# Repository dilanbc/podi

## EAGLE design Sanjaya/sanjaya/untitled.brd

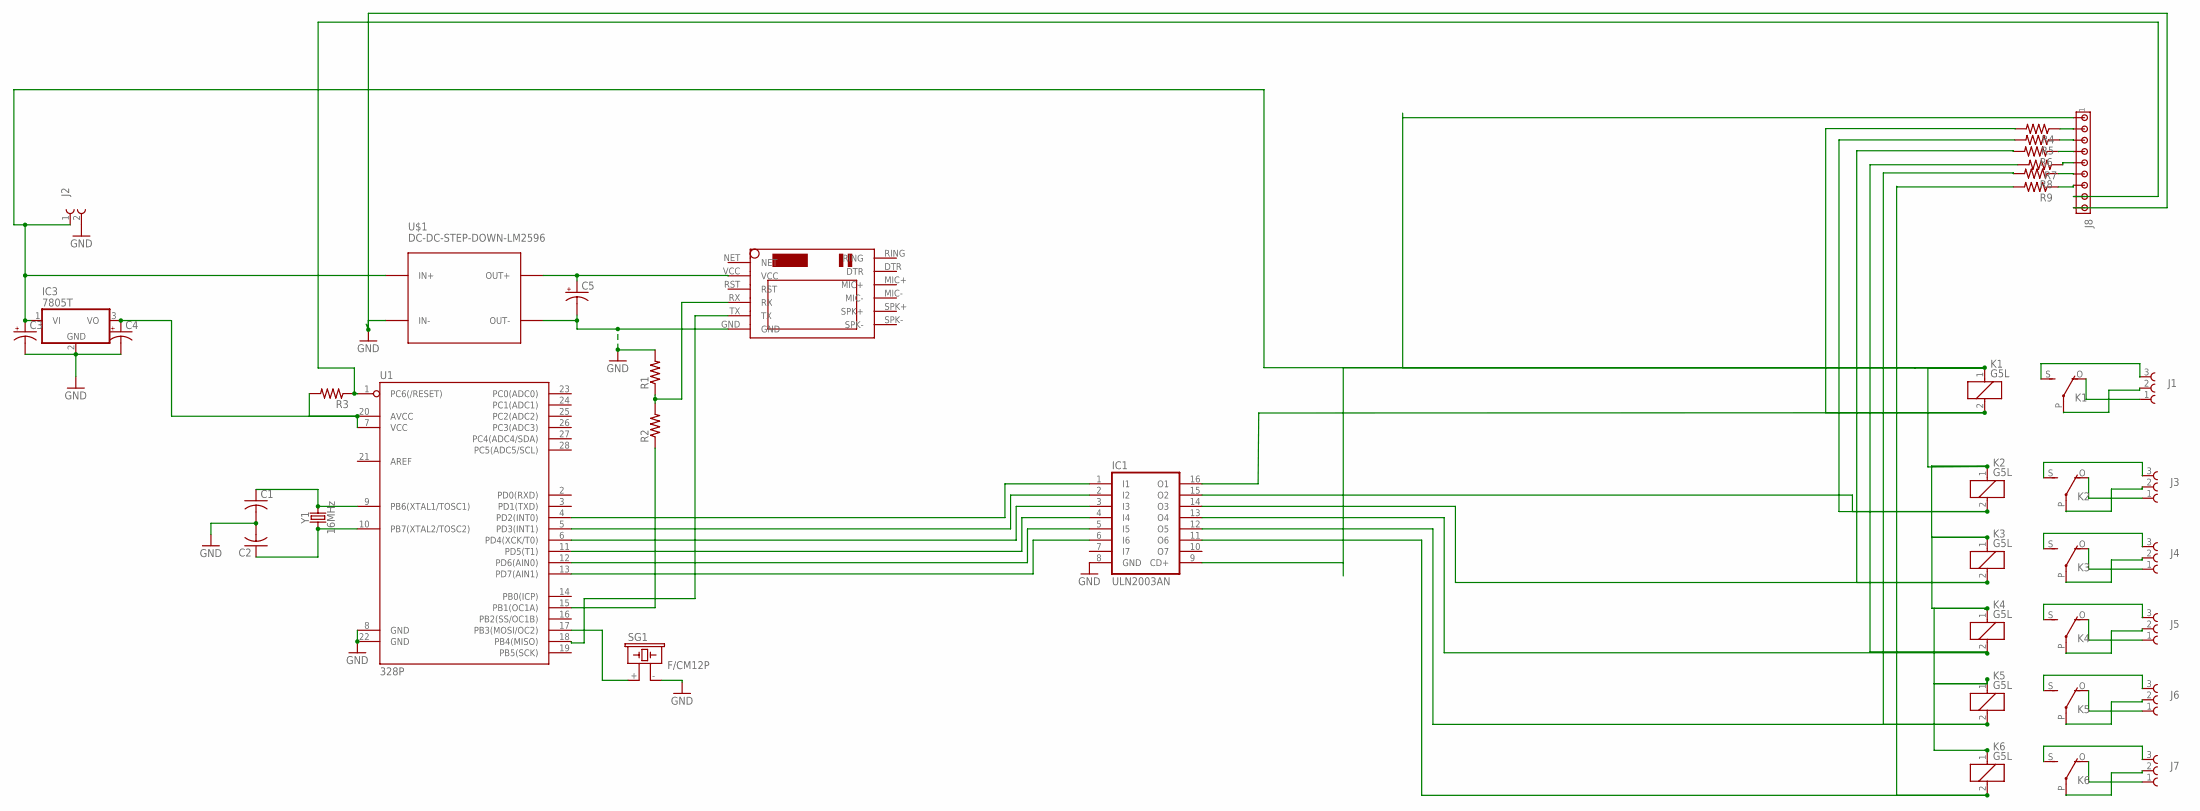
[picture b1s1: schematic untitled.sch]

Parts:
C1, C2: C-US025-024X044; C025-024X044
C3, C4: CPOL-USE2.5-5; E2,5-5
C5: CAPACITOR-PE5-8.5; E5-8,5
IC1: ULN2003AN; DIL16
IC3: 7805T; TO220H
J1, J3, J4, J5, J6, J7: 691216700003
J2: 691217910002
J8: MTA09-100; 10X09MTA
K1, K2, K3, K4, K5, K6: G5L; G5LE
R1, R2, R3, R4, R5, R6, R7, R8, R9: R-US_0204/7; 0204/7
SG1: F/CM12P
U1: 328P; DIP28
U$1: DC-DC-STEP-DOWN-LM2596
U$2: SIM800LMODULE
Y1: 16MHz; HC49US

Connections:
GND: C1.2, C2.2, C3.-, C4.-, C5.-, IC1.8 (GND), IC3.2 (GND), J2.2, J8.9, R1.2, SG1.- (2), U1.8 (GND), U1.22 (GND), U$1.IN-, U$1.OUT-, U$2.GND
unnamed: IC1.1 (I1), U1.4 (PD2(INT0))
unnamed: C2.1, U1.10 (PB7(XTAL2/TOSC2)), Y1.1
unnamed: C1.1, U1.9 (PB6(XTAL1/TOSC1)), Y1.2
unnamed: IC1.2 (I2), U1.5 (PD3(INT1))
unnamed: IC1.3 (I3), U1.6 (PD4(XCK/T0))
unnamed: IC1.4 (I4), U1.11 (PD5(T1))
unnamed: IC1.5 (I5), U1.12 (PD6(AIN0))
unnamed: IC1.6 (I6), U1.13 (PD7(AIN1))
unnamed: IC1.15 (O2), K2.2, R5.2
unnamed: C4.+, IC3.3 (VO), R3.2, U1.7 (VCC), U1.20 (AVCC)
unnamed: J8.2, R4.1
unnamed: IC1.14 (O3), K3.2, R6.2
unnamed: IC1.13 (O4), K4.2, R7.2
unnamed: C5.+, U$1.OUT+, U$2.VCC
unnamed: U1.18 (PB4(MISO)), U$2.TX
unnamed: R2.1, U1.15 (PB1(OC1A))
unnamed: R1.1, R2.2, U$2.RX
unnamed: IC1.12 (O5), K5.2, R8.2
unnamed: J1.2, K1.P
unnamed: J1.3 (1), K1.S
unnamed: J1.1 (3), K1.O
unnamed: J8.3, R5.1
unnamed: IC1.16 (O1), K1.2, R4.2
unnamed: J3.2, K2.P
unnamed: J3.3 (1), K2.S
unnamed: J3.1 (3), K2.O
unnamed: J8.8, R3.1, U1.1 (PC6(/RESET))
unnamed: J4.2, K3.P
unnamed: J4.3 (1), K3.S
unnamed: J4.1 (3), K3.O
unnamed: SG1.+ (1), U1.17 (PB3(MOSI/OC2))
unnamed: J5.2, K4.P
unnamed: J5.3 (1), K4.S
unnamed: J5.1 (3), K4.O
unnamed: J8.4, R6.1
unnamed: J6.2, K5.P
unnamed: J6.3 (1), K5.S
unnamed: J6.1 (3), K5.O
unnamed: C3.+, IC1.9 (CD+), IC3.1 (VI), J2.1, J8.1, K1.1, K2.1, K3.1, K4.1, K5.1, K6.1, U$1.IN+
unnamed: J7.2, K6.P
unnamed: J7.3 (1), K6.S
unnamed: J7.1 (3), K6.O
unnamed: J8.5, R7.1
unnamed: J8.6, R8.1
unnamed: J8.7, R9.1
unnamed: IC1.11 (O6), K6.2, R9.2

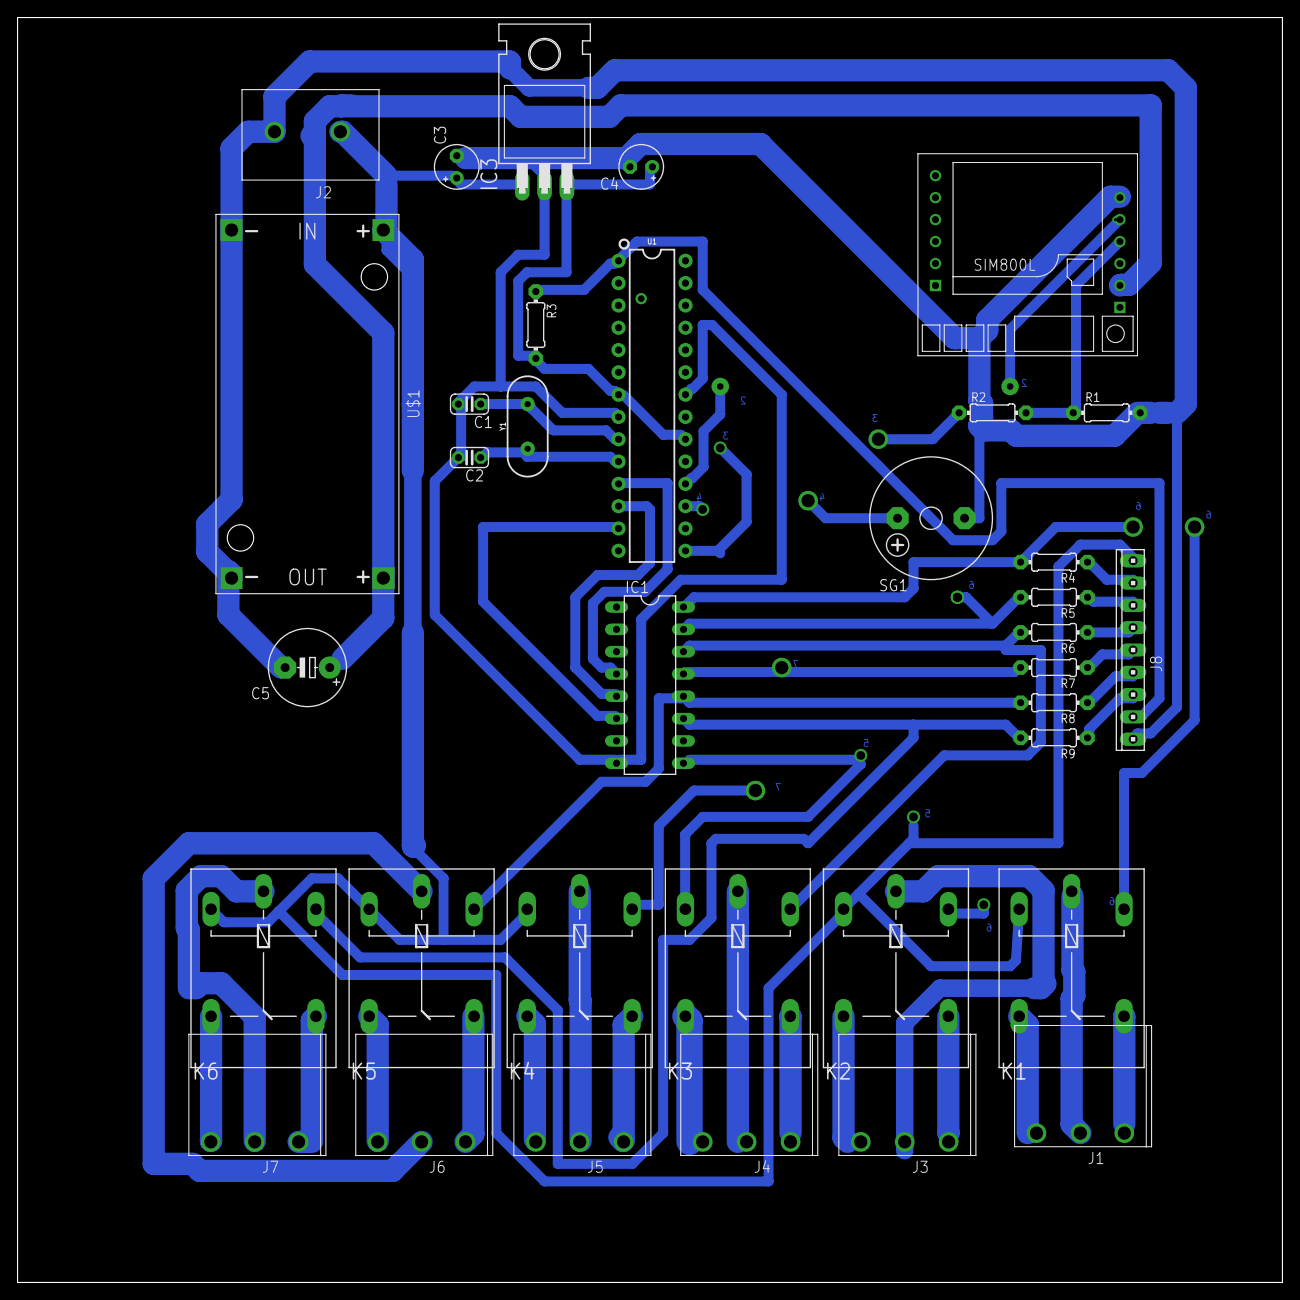
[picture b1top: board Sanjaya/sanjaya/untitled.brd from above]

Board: 2 copper layers, 144.0 x 144.0 mm, 35 parts (0 on the bottom side), 47 nets.

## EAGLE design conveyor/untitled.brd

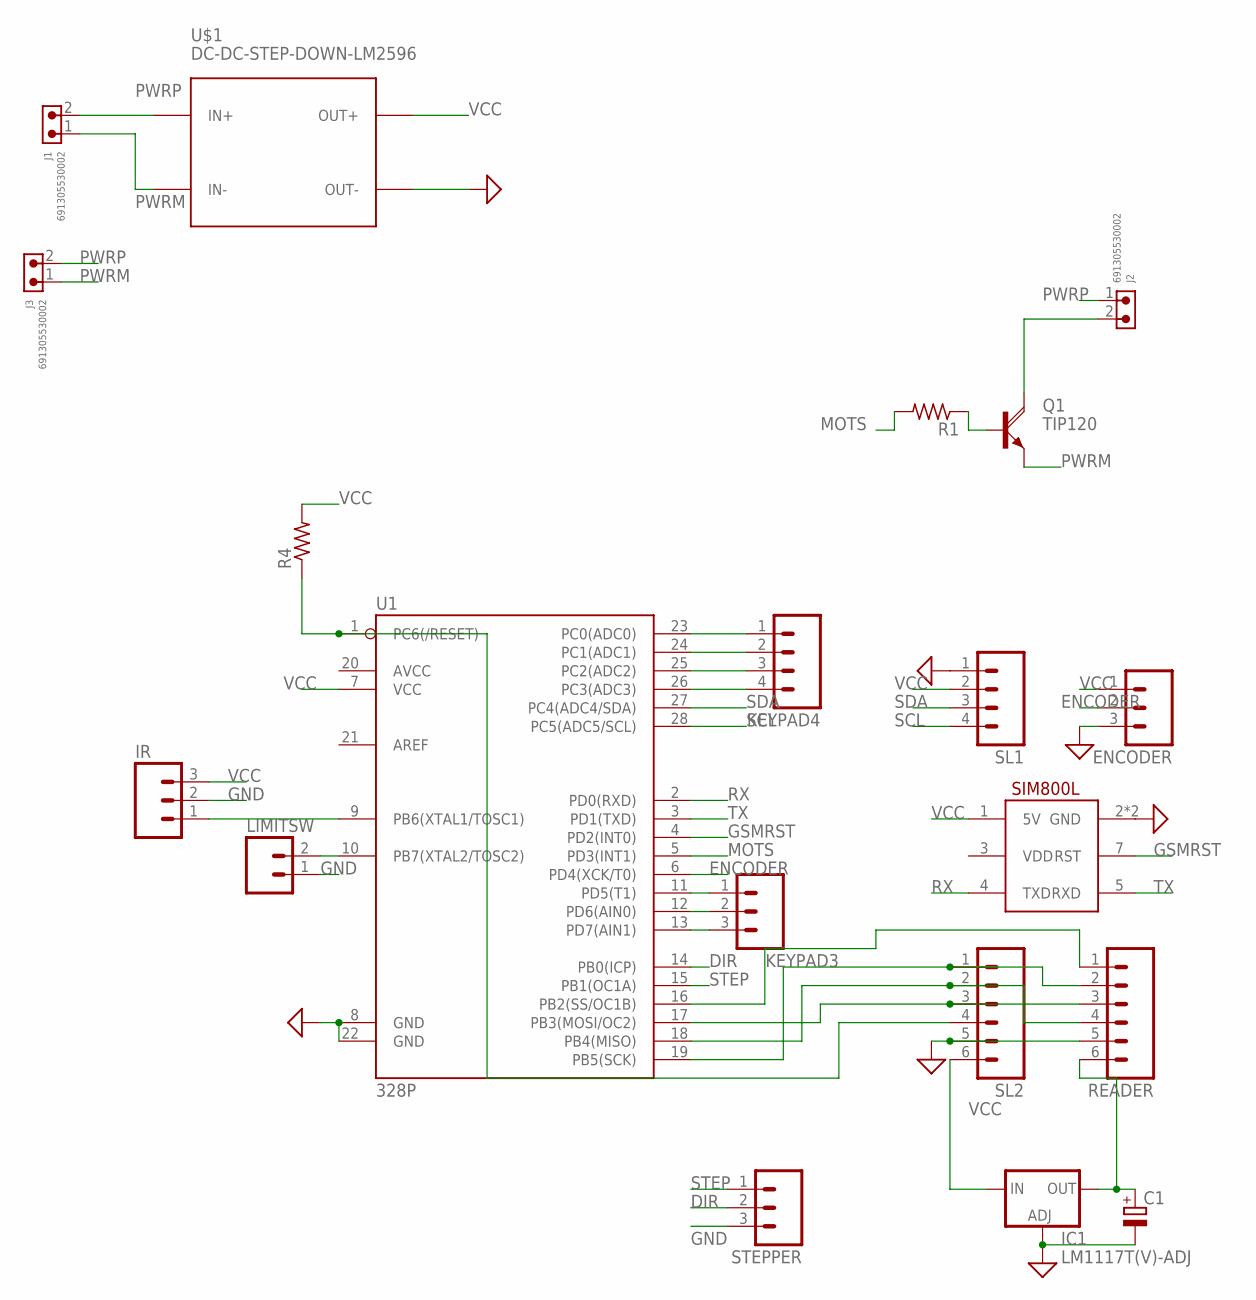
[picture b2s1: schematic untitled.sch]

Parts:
C1: CPOL-EUE5-10.5; E5-10,5
ENCODER: M03; 03P
IC1: LM1117T(V)-ADJ; TO220V
IR: M03; 03P
J1, J2, J3: 691305530002
KEYPAD3: M03; 03P
KEYPAD4: M04; 04P
LIMITSW: M02; 02P
Q1: TIP120; TO220AH
R1: R-US_0207/15; 0207/15
R4: R-US_0207/10; 0207/10
READER: M06; 06P
SL1: M04; 04P
SL2: M06; 06P
STEPPER: M03; 03P
U1: 328P; DIP28
U$1: DC-DC-STEP-DOWN-LM2596
U$2: SIM800L; SIP

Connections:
DIR: STEPPER.2, U1.14 (PB0(ICP))
ENCODER: ENCODER.2, U1.6 (PD4(XCK/T0))
GND: C1.-, ENCODER.3, IC1.1 (ADJ), IR.2, LIMITSW.1, READER.5, SL1.1, SL2.5, STEPPER.3, U1.8 (GND), U1.22 (GND), U$1.OUT-, U$2.2 (GND), U$2.6 (GND)
GSMRST: U1.4 (PD2(INT0)), U$2.7 (RST)
MOTS: R1.2, U1.5 (PD3(INT1))
unnamed: KEYPAD4.1, U1.23 (PC0(ADC0))
unnamed: LIMITSW.2, U1.10 (PB7(XTAL2/TOSC2))
unnamed: KEYPAD4.2, U1.24 (PC1(ADC1))
unnamed: READER.2, SL2.1, U1.19 (PB5(SCK))
unnamed: READER.4, SL2.2, U1.18 (PB4(MISO))
unnamed: READER.3, SL2.3, U1.17 (PB3(MOSI/OC2))
unnamed: R4.1, SL2.4, U1.1 (PC6(/RESET))
unnamed: KEYPAD4.3, U1.25 (PC2(ADC2))
unnamed: KEYPAD4.4, U1.26 (PC3(ADC3))
unnamed: KEYPAD3.1, U1.11 (PD5(T1))
unnamed: KEYPAD3.2, U1.12 (PD6(AIN0))
unnamed: KEYPAD3.3, U1.13 (PD7(AIN1))
unnamed: READER.1, U1.16 (PB2(SS/OC1B))
unnamed: C1.+, IC1.2 (OUT), READER.6
unnamed: Q1.B, R1.1
unnamed: J2.2, Q1.C
unnamed: IR.1, U1.9 (PB6(XTAL1/TOSC1))
PWRM: J1.1, J3.1, Q1.E, U$1.IN-
PWRP: J1.2, J2.1, J3.2, U$1.IN+
RX: U1.2 (PD0(RXD)), U$2.4 (TXD)
SCL: SL1.4, U1.28 (PC5(ADC5/SCL))
SDA: SL1.3, U1.27 (PC4(ADC4/SDA))
STEP: STEPPER.1, U1.15 (PB1(OC1A))
TX: U1.3 (PD1(TXD)), U$2.5 (RXD)
VCC: ENCODER.1, IC1.3 (IN), IR.3, R4.2, SL1.2, SL2.6, U1.7 (VCC), U$1.OUT+, U$2.1 (5V)

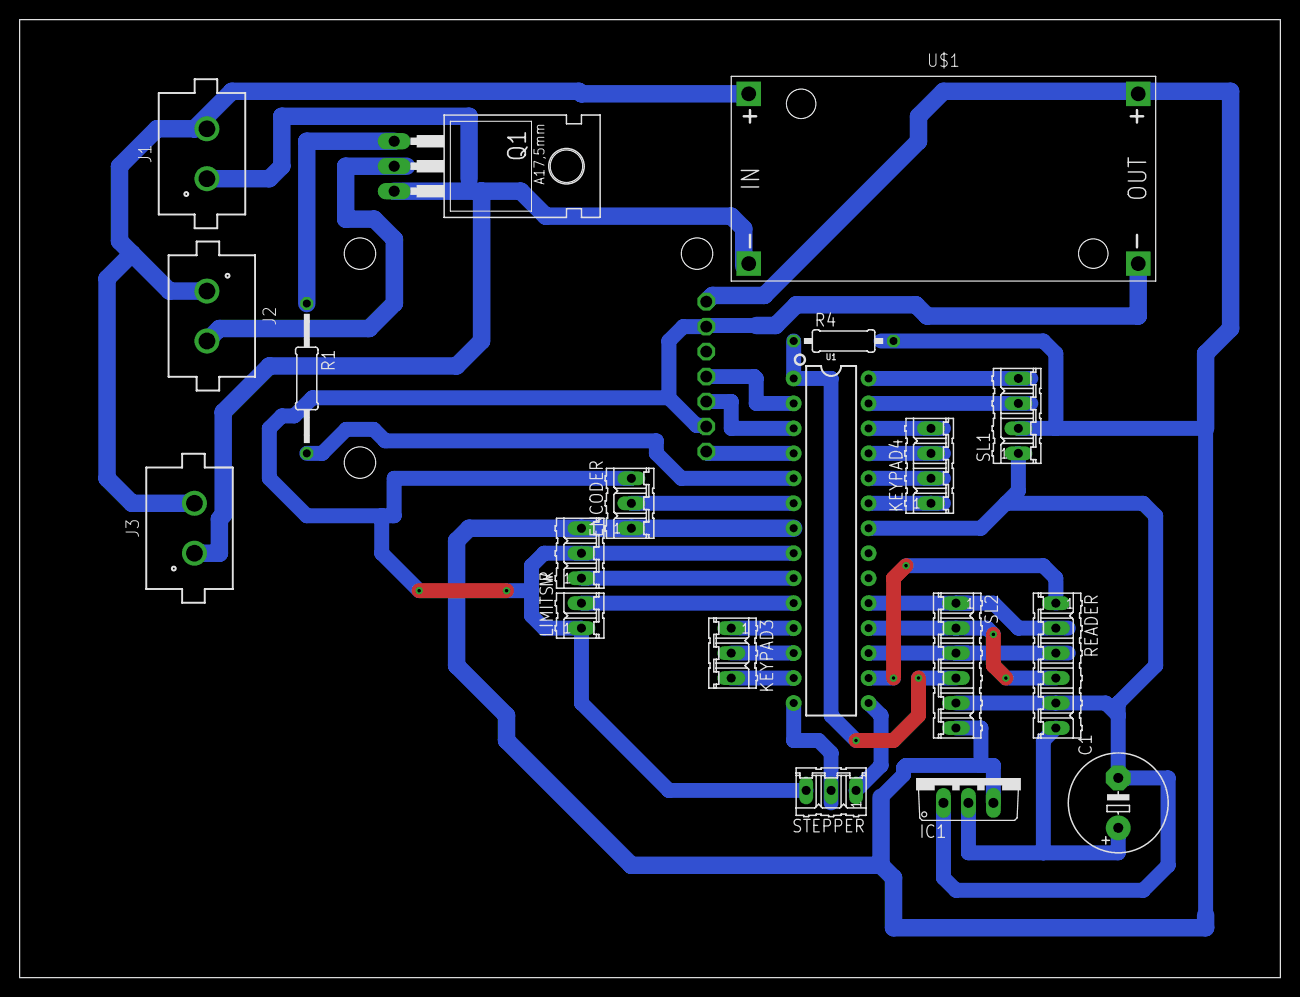
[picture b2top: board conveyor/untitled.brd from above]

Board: 2 copper layers, 128.2 x 97.5 mm, 20 parts (0 on the bottom side), 30 nets.

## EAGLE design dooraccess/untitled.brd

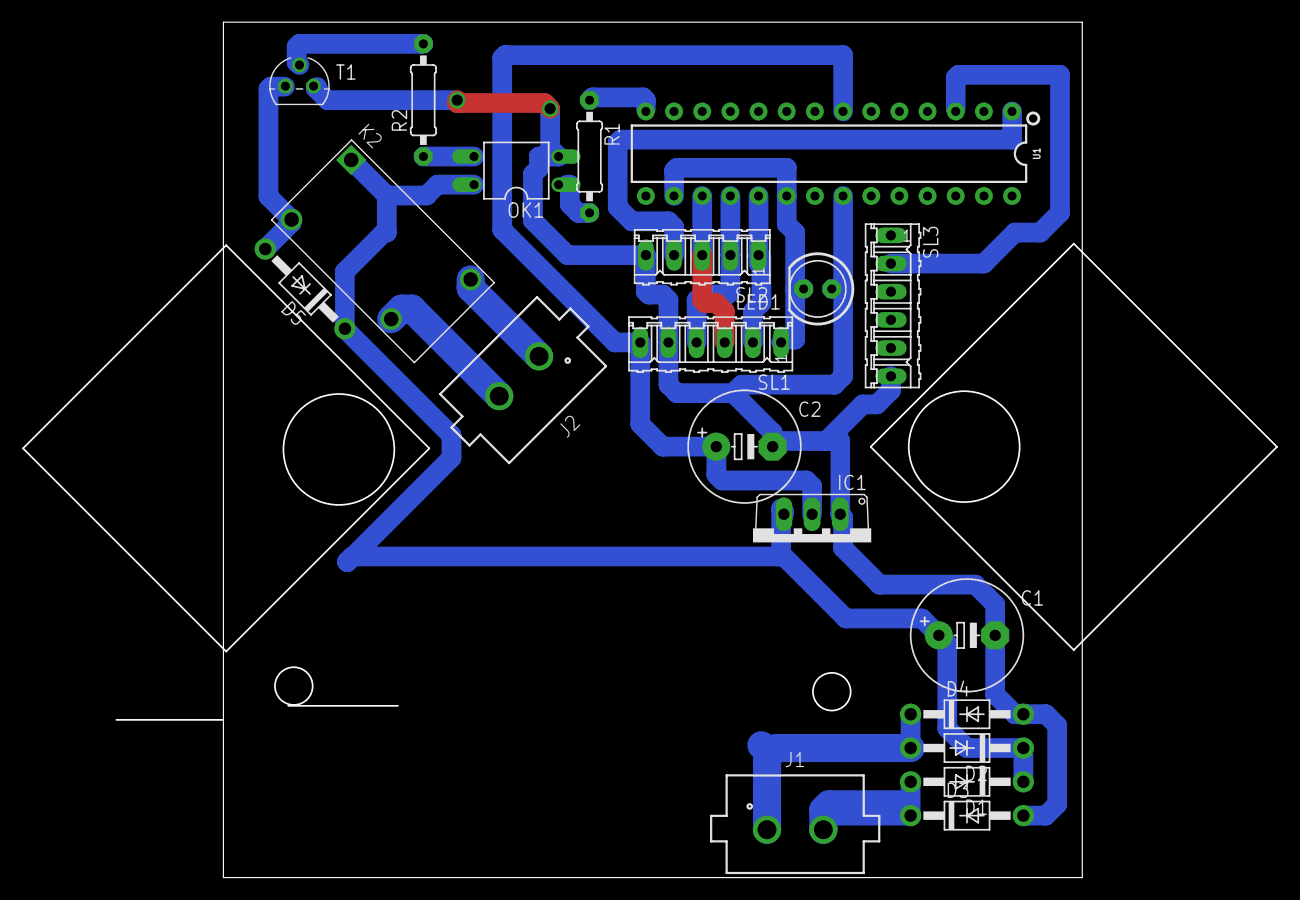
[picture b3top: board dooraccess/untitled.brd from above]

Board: 2 copper layers, 113.1 x 77.1 mm, 20 parts (0 on the bottom side), 18 nets.

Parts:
C1, C2: E5-10,5
D1, D2, D3, D4, D5: 1N4004; DO41-10
IC1: LM1117T(V)-ADJ; TO220V
J1, J2: 691305530002
K2: OJE-SH-112HM,000
LED1: LED5MM
OK1: PC817; DIL04
R1, R2: 0207/10
SL1, SL3: 06P
SL2: 05P
T1: BC547; TO92
U1: 328P; DIP28

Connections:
GND: C1.-, C2.-, D3.A, D4.A, IC1.1, LED1.A, OK1.2, SL1.5, SL2.5, SL3.6, T1.1, U1.8, U1.22
HVCC: C1.+, D1.C, D2.C, D5.C, IC1.3, K2.A1, OK1.4
unnamed: D1.A, D3.C, J1.2
unnamed: SL1.2, SL2.1, U1.19
unnamed: LED1.K, SL1.1, U1.16, U1.20
unnamed: D5.A, K2.A2, T1.3
unnamed: D2.A, D4.C, J1.1
unnamed: SL1.4, SL2.2, U1.18
unnamed: SL1.3, SL2.3, U1.17
unnamed: SL2.4, U1.1
unnamed: R1.1, U1.14
unnamed: OK1.3, R2.1
unnamed: R2.2, T1.2
unnamed: J2.1, K2.NC
unnamed: J2.2, K2.NO
OCT: OK1.1, R1.2
TX: SL3.2, U1.3
VCC: C2.+, IC1.2, SL1.6, U1.7

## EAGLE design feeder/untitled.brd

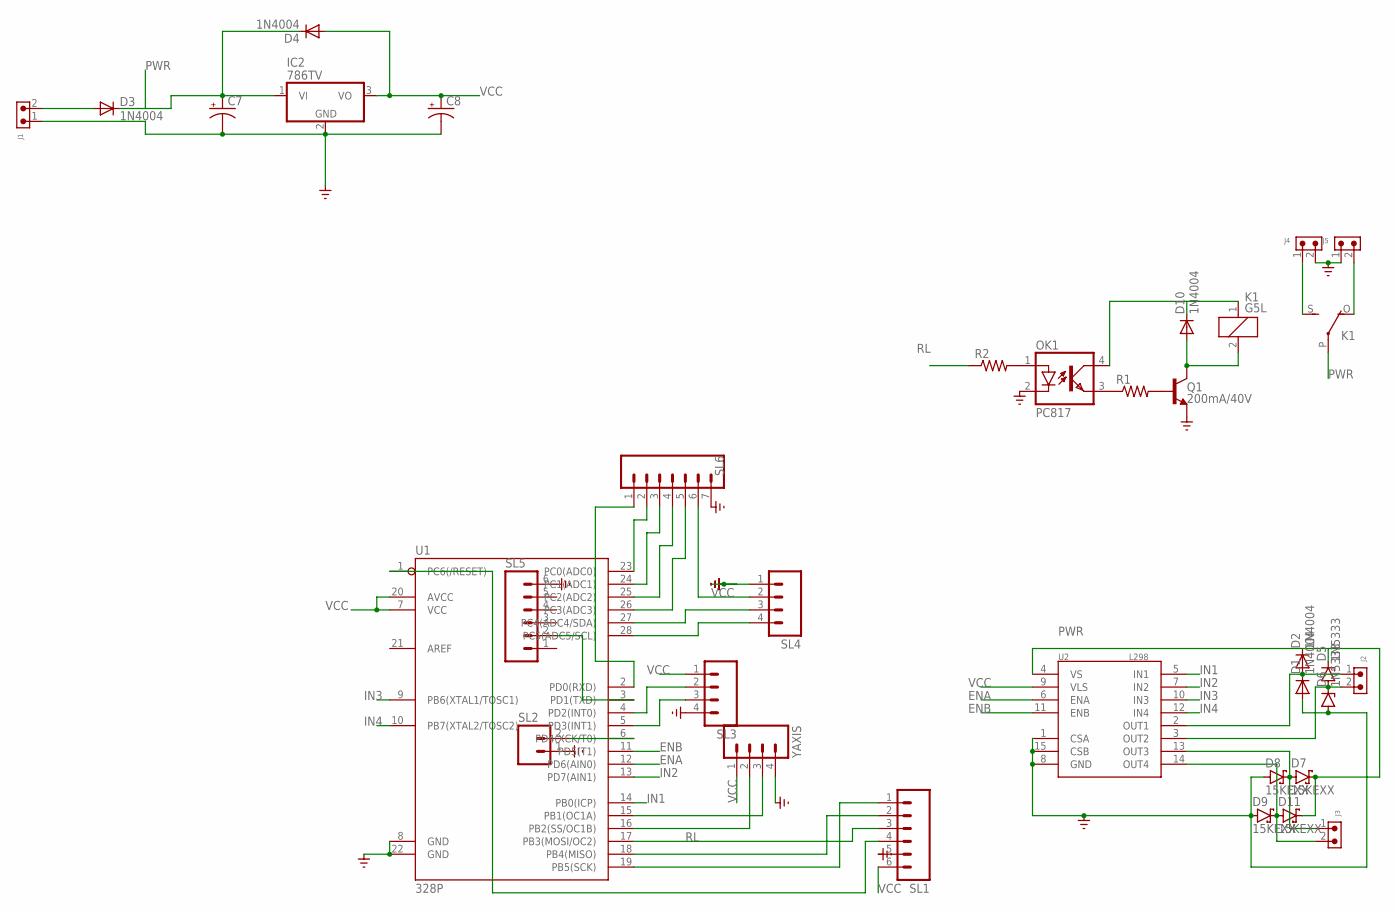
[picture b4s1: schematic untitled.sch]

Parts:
C7: CAPACITOR-PE5-10.5; E5-10,5
C8: CAPACITOR-PE5-6; E5-6
D1, D2, D3, D4, D10: 1N4004; DO41-10
D5, D6: 1N5333; C1702-15
D7, D8, D9, D11: 15KEXX; CB429-17
IC2: 786TV; TO220V
J1, J2, J3, J4, J5: 691305530002
K1: G5L; G5LE
OK1: PC817; DIL04
Q1: 200mA/40V; TO-92
R1, R2: R-US_0207/10; 0207/10
SL1, SL5: M06; 06P
SL2: M02; 02P
SL3, SL4: M04; 04P
SL6: M07; 07P
U1: 328P; DIP28
U2: L298; MULTIWATT15
YAXIS: M04; 04P

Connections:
ENA: U1.12 (PD6(AIN0)), U2.6 (ENA)
ENB: U1.11 (PD5(T1)), U2.11 (ENB)
GND: C7.-, C8.-, D1.A, D6.A, D8.A, D9.A, IC2.2 (GND), J1.1, J4.2, J5.1, OK1.2 (C), Q1.1 (E), SL1.5, SL2.1, SL3.4, SL4.1, SL5.6, SL6.7, U1.8 (GND), U1.22 (GND), U2.1 (CSA), U2.8 (GND), U2.15 (CSB), YAXIS.4
IN1: U1.14 (PB0(ICP)), U2.5 (IN1)
IN2: U1.13 (PD7(AIN1)), U2.7 (IN2)
IN3: U1.9 (PB6(XTAL1/TOSC1)), U2.10 (IN3)
IN4: U1.10 (PB7(XTAL2/TOSC2)), U2.12 (IN4)
unnamed: SL6.2, U1.23 (PC0(ADC0))
unnamed: SL3.2, U1.4 (PD2(INT0))
unnamed: SL1.1, U1.19 (PB5(SCK))
unnamed: SL1.2, U1.18 (PB4(MISO))
unnamed: SL1.4, U1.1 (PC6(/RESET))
unnamed: D1.C, D2.A, J2.1, U2.2 (OUT1)
unnamed: D5.A, D6.C, J2.2, U2.3 (OUT2)
unnamed: D7.A, D8.C, J3.1, U2.13 (OUT3)
unnamed: D9.C, D11.A, J3.2, U2.14 (OUT4)
unnamed: U1.16 (PB2(SS/OC1B)), YAXIS.2
unnamed: U1.15 (PB1(OC1A)), YAXIS.3
unnamed: SL3.3, U1.5 (PD3(INT1))
unnamed: SL2.2, U1.6 (PD4(XCK/T0))
unnamed: SL5.2, U1.3 (PD1(TXD))
unnamed: SL6.1, U1.2 (PD0(RXD))
unnamed: SL4.3, U1.27 (PC4(ADC4/SDA))
unnamed: SL4.4, U1.28 (PC5(ADC5/SCL))
unnamed: SL6.3, U1.24 (PC1(ADC1))
unnamed: SL6.4, U1.25 (PC2(ADC2))
unnamed: SL6.5, U1.26 (PC3(ADC3))
unnamed: D10.C, K1.1, OK1.4 (COL)
unnamed: J5.2, K1.O
unnamed: J4.1, K1.S
unnamed: D10.A, K1.2, Q1.3 (C)
unnamed: Q1.2 (B), R1.2
unnamed: OK1.3 (EMIT), R1.1
unnamed: OK1.1 (A), R2.2
PWR: C7.+, D2.C, D3.A, D3.C, D4.C, D5.C, D7.C, D11.C, IC2.1 (VI), J1.2, K1.P, U2.4 (VS)
RL: R2.1, SL1.3, U1.17 (PB3(MOSI/OC2))
VCC: C8.+, D4.A, IC2.3 (VO), SL1.6, SL3.1, SL4.2, SL6.6, U1.7 (VCC), U1.20 (AVCC), U2.9 (VLS), YAXIS.1

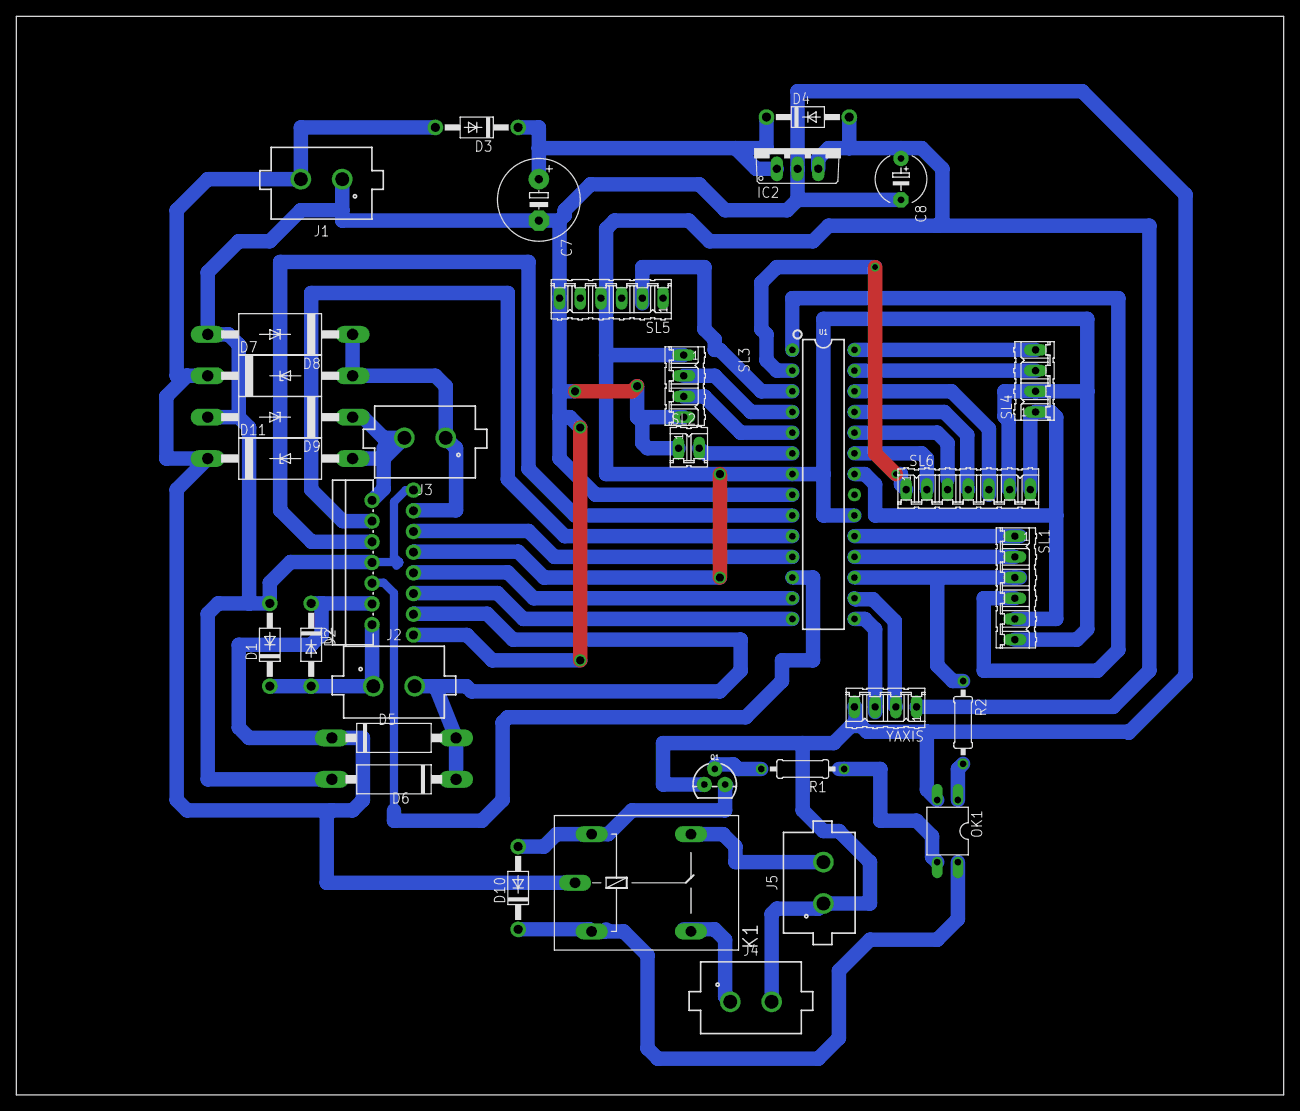
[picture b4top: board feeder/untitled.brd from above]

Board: 2 copper layers, 155.6 x 132.4 mm, 33 parts (0 on the bottom side), 37 nets.

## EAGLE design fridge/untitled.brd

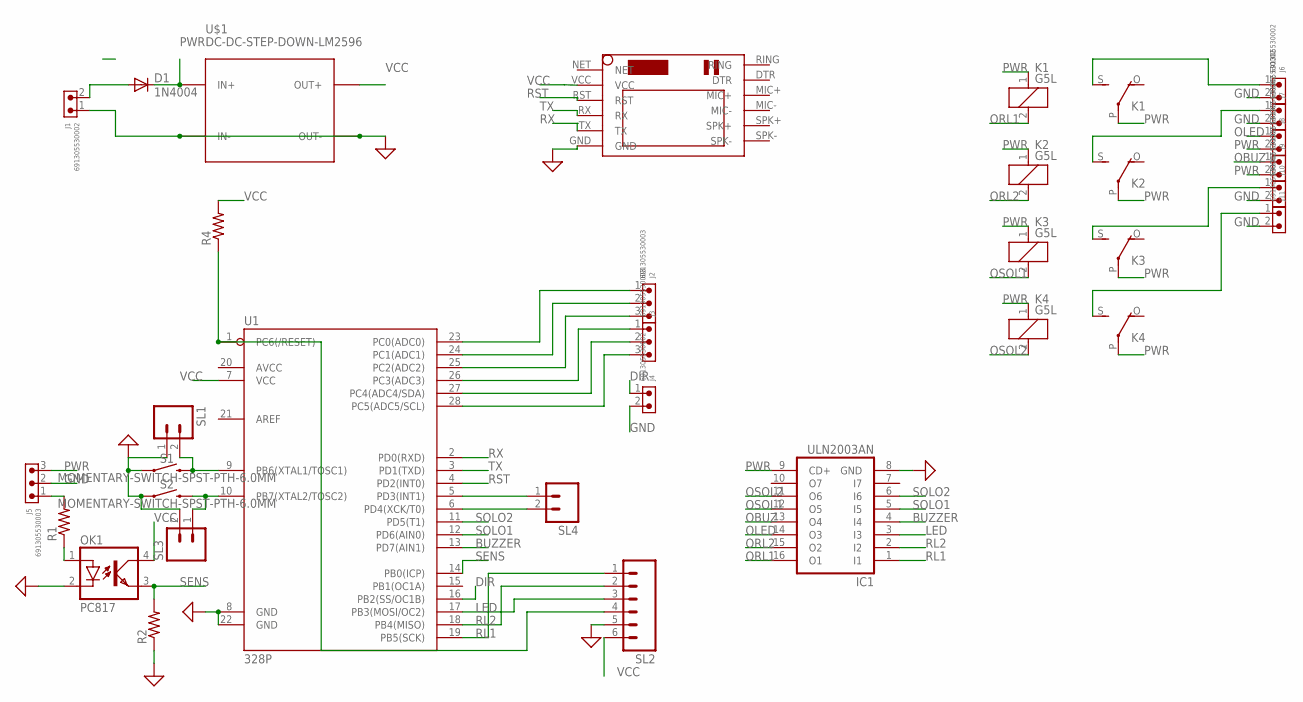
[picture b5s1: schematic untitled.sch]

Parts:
D1: 1N4004; DO41-10
IC1: ULN2003AN; DIL16
J1, J4, J6, J7, J8, J9, J10, J11: 691305530002
J2, J3, J5: 691305530003
K1, K2, K3, K4: G5L; G5LE
OK1: PC817; DIL04
R1, R2, R4: R-US_0207/10; 0207/10
S1, S2: MOMENTARY-SWITCH-SPST-PTH-6.0MM; TACTILE_SWITCH_PTH_6.0MM
SL1, SL3, SL4: M02; 02P
SL2: M06; 06P
U1: 328P; DIP28
U$1: DC-DC-STEP-DOWN-LM2596
U$2: SIM800LMODULE

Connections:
BUZZER: IC1.4 (I4), U1.13 (PD7(AIN1))
DIR: J4.1, U1.16 (PB2(SS/OC1B))
GND: IC1.8 (GND), J1.1, J4.2, J5.2, J6.2, J7.2, J10.2, J11.2, OK1.2 (C), R2.1, S1.1, S2.1, SL1.1, SL2.5, SL3.2, U1.8 (GND), U1.22 (GND), U$1.IN-, U$1.OUT-, U$2.GND
LED: IC1.3 (I3), SL2.3, U1.17 (PB3(MOSI/OC2))
unnamed: J6.1, K1.S
unnamed: J2.1, U1.23 (PC0(ADC0))
unnamed: J2.2, U1.24 (PC1(ADC1))
unnamed: J7.1, K2.S
unnamed: J10.1, K3.S
unnamed: J2.3, U1.25 (PC2(ADC2))
unnamed: J3.1, U1.26 (PC3(ADC3))
unnamed: J3.2, U1.27 (PC4(ADC4/SDA))
unnamed: J3.3, U1.28 (PC5(ADC5/SCL))
unnamed: J5.1, R1.2
unnamed: OK1.1 (A), R1.1
unnamed: S2.3 (2), SL3.1, U1.10 (PB7(XTAL2/TOSC2))
unnamed: R4.1, SL2.4, U1.1 (PC6(/RESET))
unnamed: S1.3 (2), SL1.2, U1.9 (PB6(XTAL1/TOSC1))
unnamed: J11.1, K4.S
unnamed: SL4.1, U1.5 (PD3(INT1))
unnamed: SL4.2, U1.6 (PD4(XCK/T0))
OBUZ: IC1.13 (O4), J9.1
OLED: IC1.14 (O3), J8.1
ORL1: IC1.16 (O1), K1.2
ORL2: IC1.15 (O2), K2.2
OSOL1: IC1.12 (O5), K3.2
OSOL2: IC1.11 (O6), K4.2
PWR: D1.C, IC1.9 (CD+), J5.3, J8.2, J9.2, K1.1, K1.P, K2.1, K2.P, K3.1, K3.P, K4.1, K4.P, U$1.IN+
PWRIN: D1.A, J1.2
RL1: IC1.1 (I1), SL2.1, U1.19 (PB5(SCK))
RL2: IC1.2 (I2), SL2.2, U1.18 (PB4(MISO))
RST: U1.4 (PD2(INT0)), U$2.RST
RX: U1.2 (PD0(RXD)), U$2.TX
SENS: OK1.3 (EMIT), R2.2, U1.14 (PB0(ICP))
SOLO1: IC1.5 (I5), U1.12 (PD6(AIN0))
SOLO2: IC1.6 (I6), U1.11 (PD5(T1))
TX: U1.3 (PD1(TXD)), U$2.RX
VCC: OK1.4 (COL), R4.2, SL2.6, U1.7 (VCC), U$1.OUT+, U$2.VCC

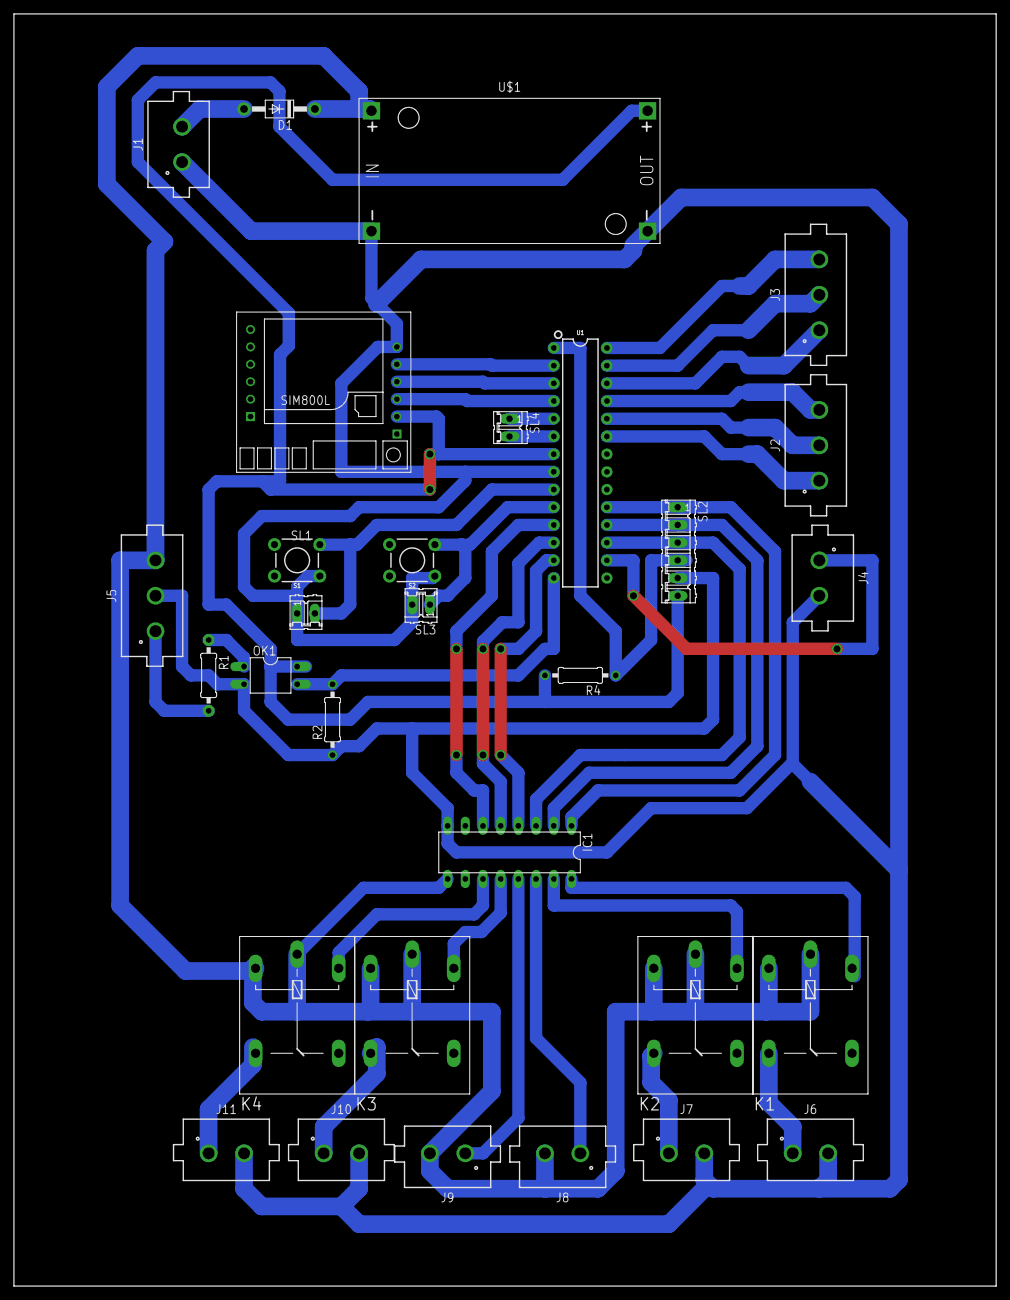
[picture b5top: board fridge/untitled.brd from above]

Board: 2 copper layers, 140.9 x 182.6 mm, 30 parts (0 on the bottom side), 38 nets.

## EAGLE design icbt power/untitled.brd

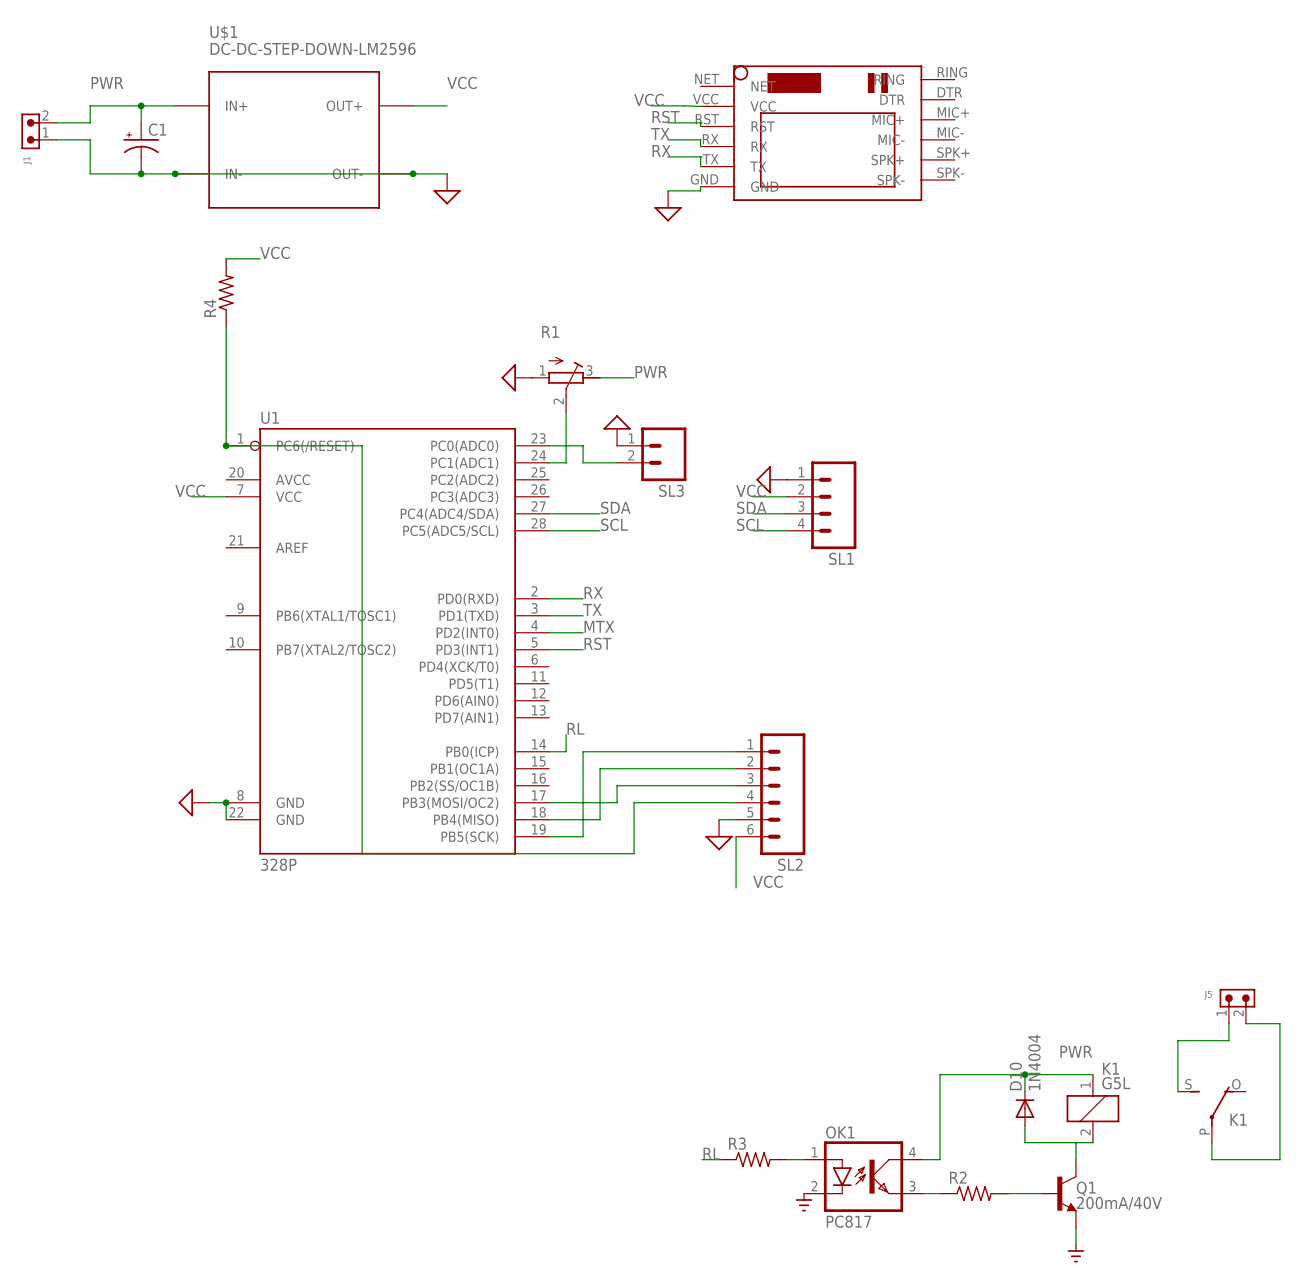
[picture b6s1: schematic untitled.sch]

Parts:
C1: CPOL-USE7.5-16; E7,5-16
D10: 1N4004; DO41-10
J1, J5: 691305530002
K1: G5L; G5LE
OK1: PC817; DIL04
Q1: 200mA/40V; TO-92
R1: R-TRIMM3296Y; RTRIM3296Y
R2, R4: R-US_0207/10; 0207/10
R3: R-US_0207/12; 0207/12
SL1: M04; 04P
SL2: M06; 06P
SL3: M02; 02P
U1: 328P; DIP28
U$1: DC-DC-STEP-DOWN-LM2596
U$2: SIM800LMODULE

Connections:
GND: C1.-, J1.1, OK1.2 (C), Q1.1 (E), R1.1 (A), SL1.1, SL2.5, SL3.1, U1.8 (GND), U1.22 (GND), U$1.IN-, U$1.OUT-, U$2.GND
MTX: U1.4 (PD2(INT0))
unnamed: OK1.1 (A), R3.2
unnamed: R1.2 (S), U1.24 (PC1(ADC1))
unnamed: SL2.1, U1.19 (PB5(SCK))
unnamed: SL2.2, U1.18 (PB4(MISO))
unnamed: SL2.3, U1.17 (PB3(MOSI/OC2))
unnamed: R4.1, SL2.4, U1.1 (PC6(/RESET))
unnamed: SL3.2, U1.23 (PC0(ADC0))
unnamed: D10.A, K1.2, Q1.3 (C)
unnamed: J5.2, K1.P
unnamed: J5.1, K1.S
unnamed: Q1.2 (B), R2.2
unnamed: OK1.3 (EMIT), R2.1
PWR: C1.+, D10.C, J1.2, K1.1, OK1.4 (COL), R1.3 (E), U$1.IN+
RL: R3.1, U1.14 (PB0(ICP))
RST: U1.5 (PD3(INT1)), U$2.RST
RX: U1.2 (PD0(RXD)), U$2.TX
SCL: SL1.4, U1.28 (PC5(ADC5/SCL))
SDA: SL1.3, U1.27 (PC4(ADC4/SDA))
TX: U1.3 (PD1(TXD)), U$2.RX
VCC: R4.2, SL1.2, SL2.6, U1.7 (VCC), U$1.OUT+, U$2.VCC

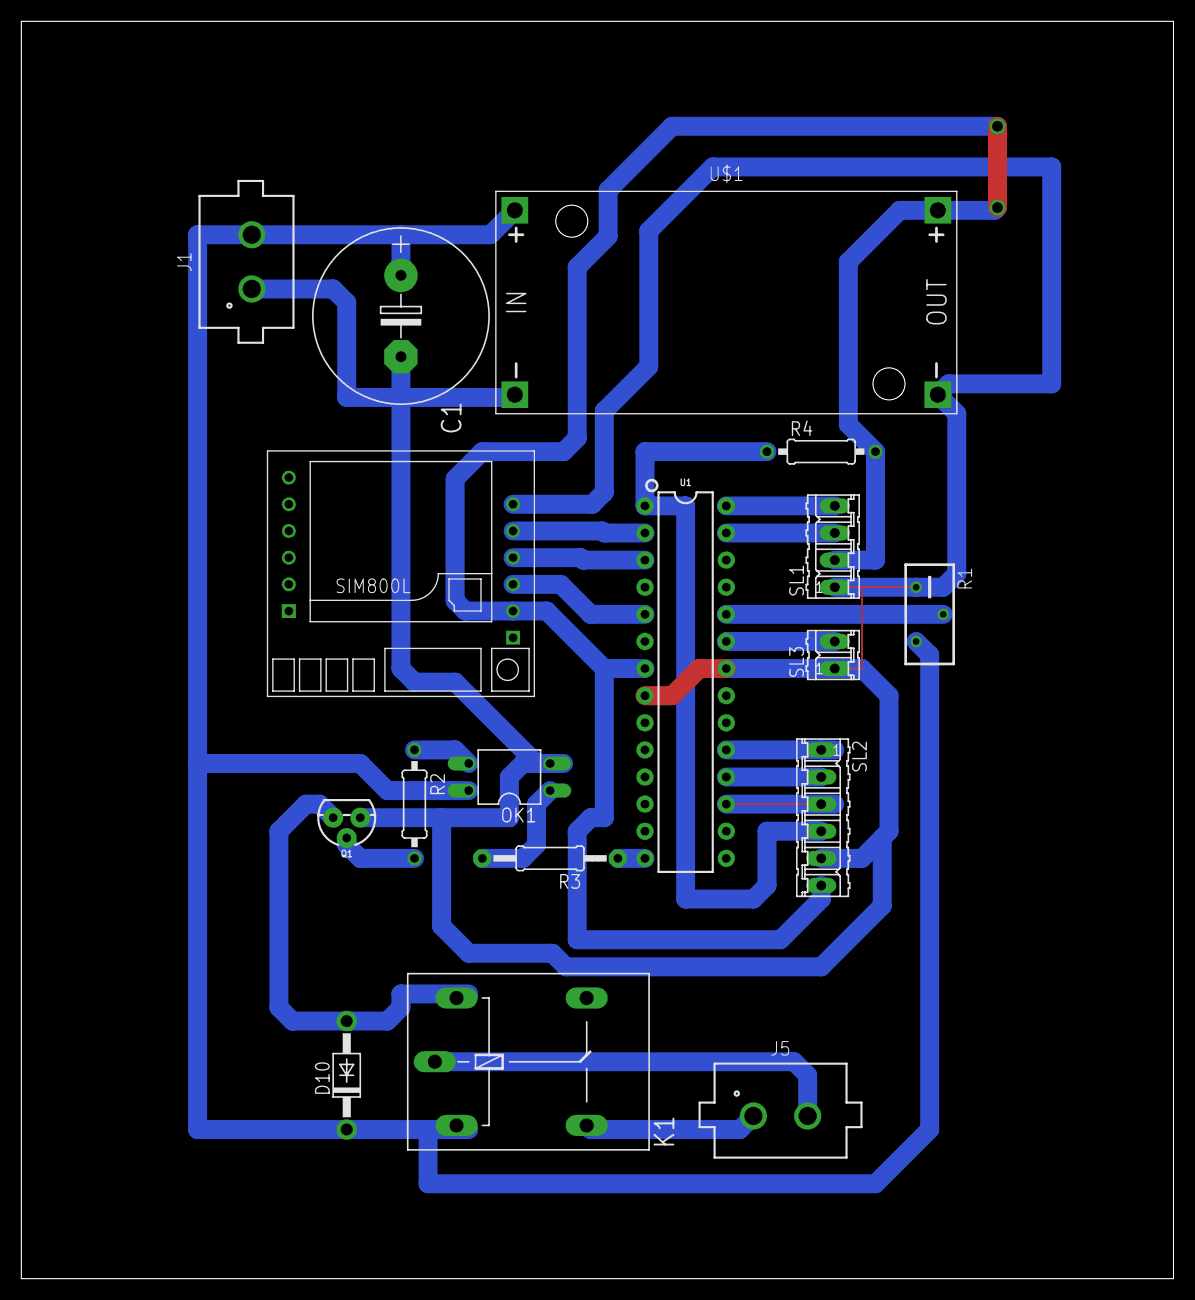
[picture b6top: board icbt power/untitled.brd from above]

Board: 2 copper layers, 107.9 x 117.8 mm, 17 parts (0 on the bottom side), 21 nets.

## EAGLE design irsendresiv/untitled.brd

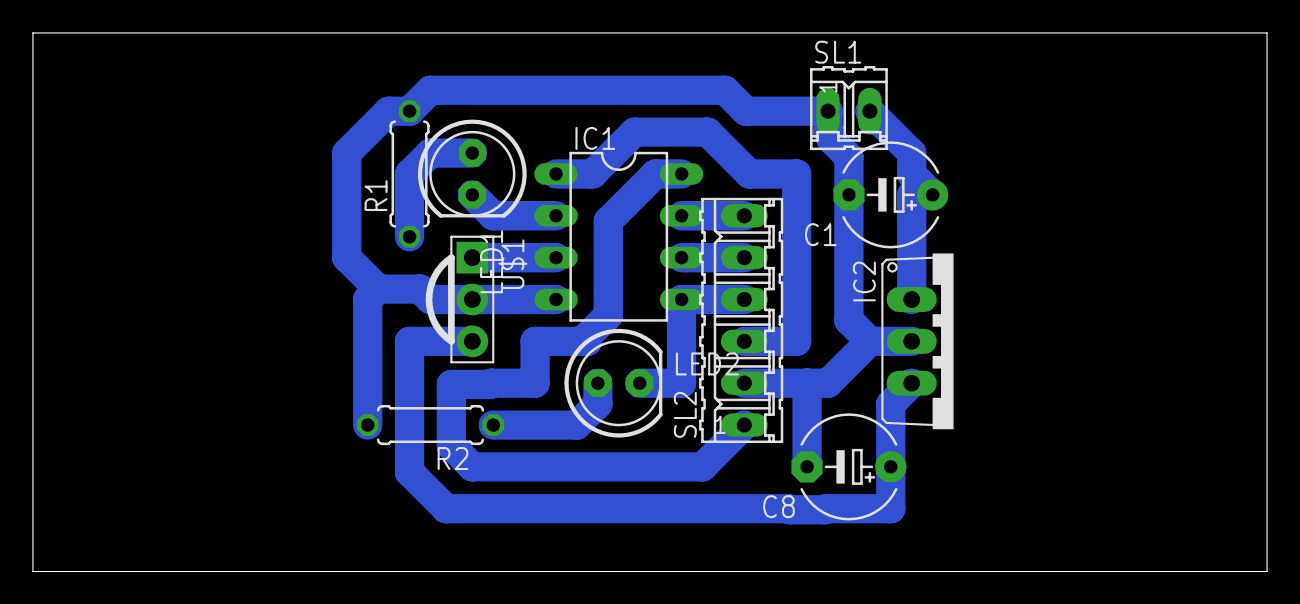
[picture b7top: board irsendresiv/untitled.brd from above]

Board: 2 copper layers, 74.9 x 32.7 mm, 11 parts (0 on the bottom side), 11 nets.

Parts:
C1, C8: E5-6
IC1: ATTINY13-20PU; DIL08
IC2: 786TV; TO220V
LED1, LED2: LED5MM
R1, R2: 0207/7
SL1: 02P
SL2: 06P
U$1: PNA460XM

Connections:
GND: C1.-, C8.-, IC1.4, IC2.2, R1.2, R2.2, SL1.1, SL2.2, U$1.2
unnamed: IC1.3, U$1.1
unnamed: IC1.2, LED1.K
unnamed: LED1.A, R1.1
unnamed: LED2.A, R2.1
unnamed: IC1.7, SL2.6
unnamed: IC1.6, SL2.5
unnamed: IC1.5, LED2.K, SL2.4
unnamed: IC1.1, SL2.3
PWR: C1.+, IC2.1, SL1.2
VCC: C8.+, IC1.8, IC2.3, SL2.1, U$1.3

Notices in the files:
parts and their libraries:
SparkFun-IC-Microcontroller: Licensing: Creative Commons ShareAlike 4.0 International - https://creativecommons.org/licenses/by-sa/4.0
Wurth_Elektronik_Passive_Capacitors_rev1: Copyright: Würth Elektronik
